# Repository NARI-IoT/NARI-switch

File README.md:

# NARI Smart Home

Progressive web app + ESP-01S firmware for NARI smart switches. Control over home Wi-Fi (LAN) with automatic cloud (MQTT) fallback. Installable, works offline on the local network, and supports real over-the-air firmware updates.

## Repository layout

| Path | Purpose |
|---|---|
| `index.html`, `css/`, `js/` | The web app (no build step) |
| `sw.js` | Service worker (offline app shell) |
| `vendor/` | Bundled third-party libraries (no CDN needed) |
| `firmware/nari_switch_esp01s.ino` | Device firmware |
| `firmware/version.json` | OTA release manifest |
| `js/config.local.js` | **Your secrets - git-ignored.** Copy from `js/config.local.example.js` |

## Run locally

```bash
npx http-server . -p 8080 -c-1
```
Open http://localhost:8080. Use `http://` locally if you want LAN control (see "LAN vs HTTPS" below).

## Configure a deployment

1. `copy js\config.local.example.js js\config.local.js` and fill in broker URL/credentials/LAN token.
2. The LAN token must equal the device's auth key (`DEFAULT_AUTH_KEY` in the sketch).
3. Never commit `config.local.js`. Rotate any credentials that were ever committed - git history keeps them.

## Firmware & OTA updates

Device contract (see `js/transport.js`): `/ping`, `/toggle?state=`, `/setBootState?mode=`, `/ota?url=` (all need `?k=KEY`), plus MQTT `nari/<id>/{set,state,status,ota,ota/progress,ota/error,config/boot}`.

**Release process**
1. Bump `FW_VERSION` in the sketch and `version` in `firmware/version.json` (must match).
2. Arduino IDE (ESP8266 core): *Sketch > Export Compiled Binary*, board "Generic ESP8266 / ESP-01S 1MB", flash size **1MB (FS:64KB OTA:~470KB)**.
3. Host the `.bin` over plain **`http://`** at the `binUrl` in `version.json` (the ESP-01S cannot do TLS reliably). The Oracle Always-Free VM + nginx works at zero cost.
4. Deploy the web app. Users see "Update Available" in the device settings.

**Important:** devices running firmware older than 1.2.0 do not have the OTA endpoints. Flash them **once** over USB/serial; after that all updates are wireless. Test every release on one switch before publishing the `.bin`.

The app only reports success when the device itself comes back reporting the new version; otherwise it shows a timeout error.

## LAN vs HTTPS

Browsers block `http://` (LAN device) requests from an `https://` page. Options: use cloud (MQTT over `wss://`) when on HTTPS; or serve the app over `http://` on the LAN; or wrap it in an Android/iOS shell. Cloud mode requires `wss://` on the broker (free TLS via Let's Encrypt + a free domain such as DuckDNS).

## Zero-cost operating notes (read before scaling)

Free hosting for the static app: GitHub Pages or Cloudflare Pages (unlimited bandwidth). Free broker: Oracle Always-Free VM running Mosquitto/EMQX.

Before selling at scale, address these - they are the real limits of a zero-cost stack:

1. **One shared MQTT login = anyone can control everyone.** Do not ship the same `nari_admin` credentials to every customer. Use per-device credentials with topic ACLs (each device/customer may only access `nari/<their-id>/#`).
2. **Firebase free (Spark) quotas** are ~50k reads / 20k writes **per day** for the whole project; they will be exhausted well before 50k users if the app syncs on every action. Keep Firestore for low-frequency data only (device list, sharing), and keep switching traffic on MQTT/LAN.
3. **One free VM has a connection ceiling.** Plan for tens of thousands of concurrent MQTT connections per tuned instance (use the ARM Ampere A1 free shape: up to 4 cores / 24 GB), not 100k on a tiny VM. Shard by customer group when needed.
4. **OTA bandwidth:** 100k devices x ~400 KB = ~40 GB per release. Fine for Oracle's free egress allowance, but roll out in batches rather than all at once.
5. **Legal pages** (Privacy Policy, Terms) are still needed before app-store or paid distribution.

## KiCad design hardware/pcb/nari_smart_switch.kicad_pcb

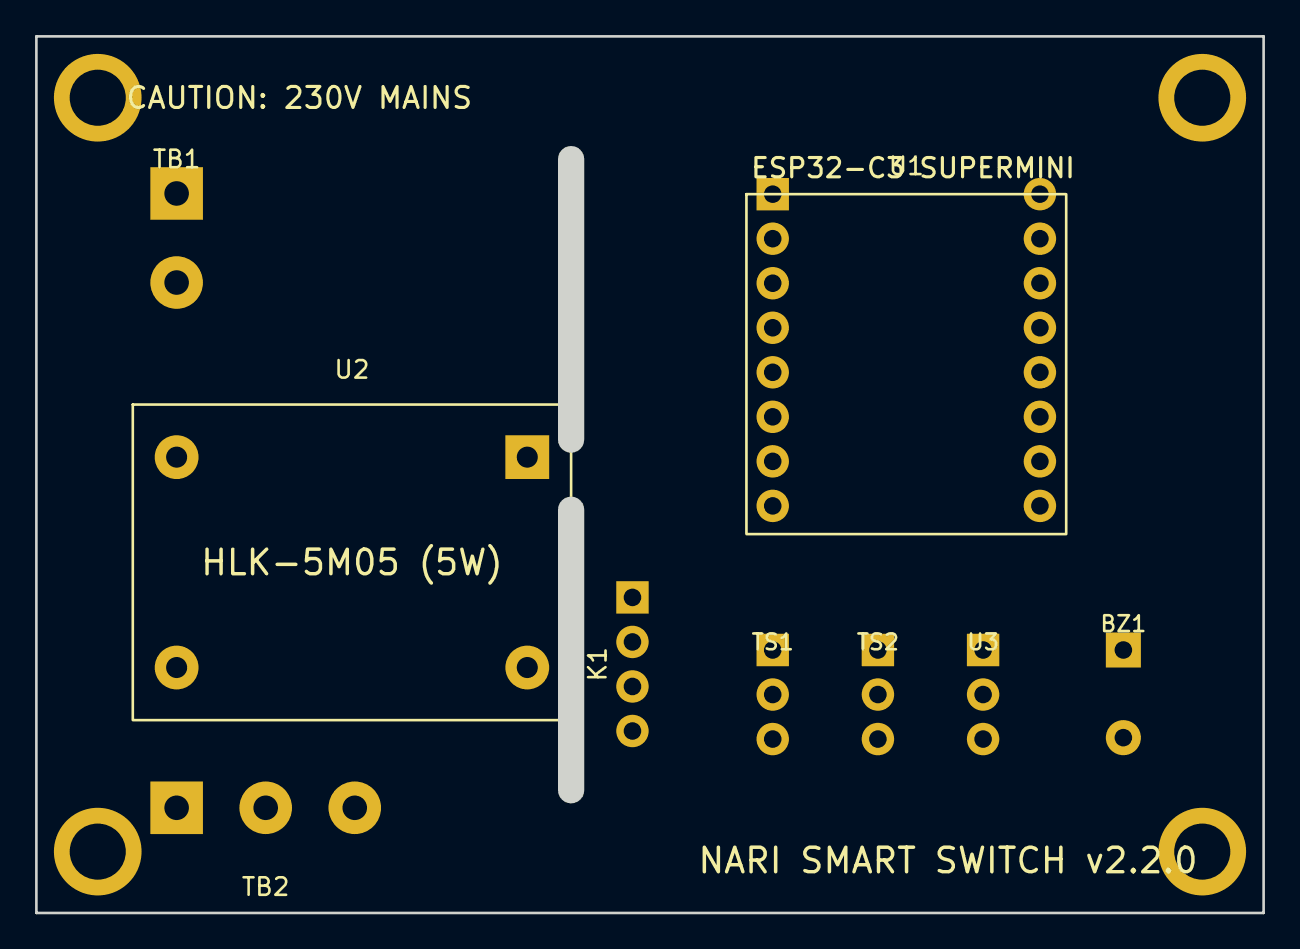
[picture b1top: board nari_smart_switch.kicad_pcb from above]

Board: 2 copper layers, 70.0 x 50.0 mm, 9 parts (0 on the bottom side), 11 nets, no tracks yet.

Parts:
BZ1: Buzzer_12x9.5RM7.6
K1: PinHeader_1x04_P2.54mm_Vertical
TB1: TerminalBlock_Phoenix_MKDS-1,5-2-5.08
TB2: TerminalBlock_Phoenix_MKDS-1,5-3-5.08
TS1, TS2: PinHeader_1x03_P2.54mm_Vertical
U1: ESP32-C3-SuperMini
U2: Converter_ACDC_HiLink_HLK-5Mxx
U3: IRReceiver_Vishay_CAST-3pin

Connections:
+3.3V: TS1.1, TS2.1, U1.3, U3.3
+5V: K1.4, U1.1, U2.4
AC_FUSED: TB2.3, U2.1
AC_NEUTRAL: TB1.2, U2.2
GND: BZ1.2, K1.1, TS1.2, TS2.2, U1.2, U2.3, U3.2
GPIO0_TOUCH1: TS1.3, U1.4
GPIO1_TOUCH2: TS2.3, U1.5
GPIO3_IRRECV: U1.7, U3.1
GPIO5_RELAY1: K1.2, U1.9
GPIO6_RELAY2: K1.3, U1.10
GPIO7_BUZZER: BZ1.1, U1.11
